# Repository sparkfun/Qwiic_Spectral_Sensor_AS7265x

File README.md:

SparkFun Triad Spectroscopy Sensor - AS7265x (Qwiic)
===========================================================

[*SparkFun Triad Spectroscopy Sensor (SEN-15050)*](https://www.sparkfun.com/products/15050)

The SparkFun Triad Spectroscopy Sensor is a powerful optical inspection sensor. Three AS7265x sensors are combined alongside a visible, UV, and IR LEDs to illuminate and test various surfaces for light spectroscopy. The Triad detects 18 discrete channels of light from 372nm (UV) to 966nm (IR) enabling desktop spectroscopy.

What can you do with light spectroscopy? It’s an amazing field of study, and the SparkFun Triad brings what used to be prohibitively expensive equipment to the desktop. The AS7265x should not be confused with highly complex mass spectrometers, but the sensor array does give the user the ability to measure and characterize how different materials absorb and reflect 18 different frequencies of light.

Want to use this board using python? Checkout hwreverse [pySectralTriad](https://github.com/hwreverse/pySpectralTriad)!

**Thanks to:**

* **pySpectralTriad** for the python application

Repository Contents
-------------------

* **/Documents** - Sensor and LED datasheets
* **/Hardware** - Eagle files

Documentation
--------------

* **[Installing an Arduino Library Guide](https://learn.sparkfun.com/tutorials/installing-an-arduino-library)** - Basic information on how to install an Arduino library.
* **[Arduino Library](https://github.com/sparkfun/SparkFun_AS7265x_Arduino_Library)** - Arduino Library for the SparkFun Triad Spectroscopy Sensor.
* **[Hookup Guide](https://learn.sparkfun.com/tutorials/spectral-triad-as7265x-hookup-guide)** - Basic hookup guide for the SparkFun Triad Spectroscopy Sensor.

License Information
-------------------

This product is _**open source**_! 

Various bits of the code have different licenses applied. Anything SparkFun wrote is beerware; if you see me (or any other SparkFun employee) at the local, and you've found our code helpful, please buy us a round!

Please use, reuse, and modify these files as you see fit. Please maintain attribution to SparkFun Electronics and release anything derivative under the same license.

Distributed as-is; no warranty is given.

- Your friends at SparkFun.

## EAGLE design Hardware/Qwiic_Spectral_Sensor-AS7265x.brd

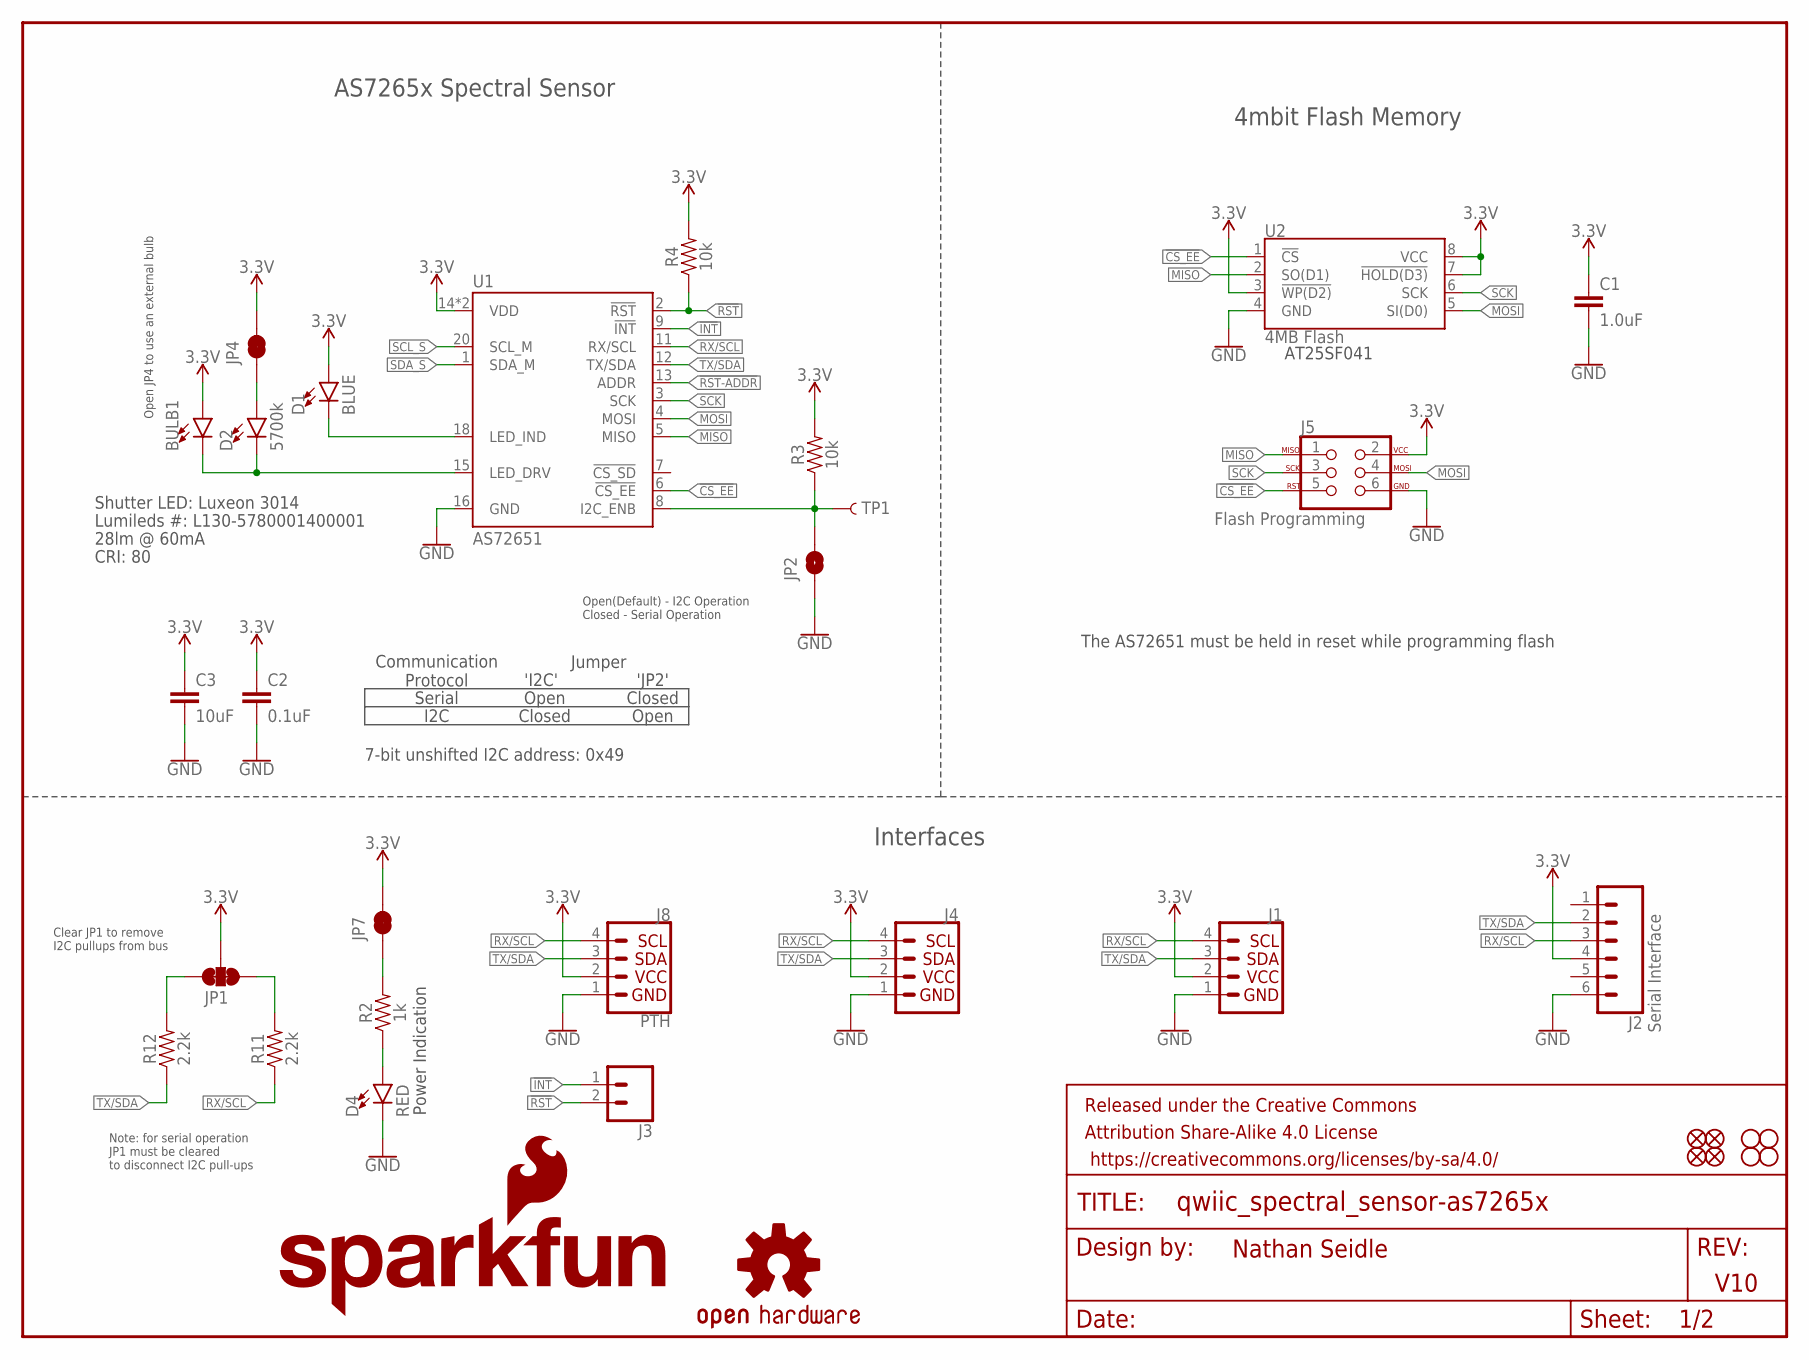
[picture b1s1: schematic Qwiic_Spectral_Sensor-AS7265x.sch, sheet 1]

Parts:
BULB1: LEDNS; LED_5MM_NOSILK
C1: 1.0uF; 0603
C2: 0.1uF; 0603
C3: 10uF; 0603
D1: BLUE; LED-0603
D2: 5700k; SUPER_BRIGHT_SMD_LED_3014
D4: RED; LED-0603
FD1, FD2, FD3, FD4: FIDUCIAL1X2; FIDUCIAL-1X2
FRAME1: FRAME-LETTER; CREATIVE_COMMONS
H1, H2, H3, H4: STAND-OFF
J1, J4: QWIIC_CONNECTORJS-1MM; 1X04_1MM_RA
J2: Serial Interface; 1X06_NO_SILK
J3: CONN_021X02_NO_SILK; 1X02_NO_SILK
J5: Flash Programming; 2X3_TEST_POINTS
J8: PTH; 1X04_NO_SILK
JP1: JUMPER-SMT_3_2-NC_TRACE_SILK; SMT-JUMPER_3_2-NC_TRACE_SILK
JP2: JUMPER-SMT_2_NO_SILK; SMT-JUMPER_2_NO_SILK
JP4, JP7: JUMPER-SMT_2_NC_TRACE_NO-SILK; SMT-JUMPER_2_NC_TRACE_NO-SILK
LOGO1: SFE_LOGO_NAME_FLAME.1_INCH; SFE_LOGO_NAME_FLAME_.1
LOGO4: OSHW-LOGOS; OSHW-LOGO-S
R2: 1k; 0603
R3, R4: 10k; 0603
R11, R12: 2.2k; 0603
TP1: TEST-POINT3; PAD.03X.03
U1: AS72651; LGA20
U2: 4MB Flash; SO08

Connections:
3.3V: BULB1.A, C1.1, C2.1, C3.1, D1.A, J1.2, J2.4, J4.2, J5.2, J8.2, JP1.2, JP4.2, JP7.2, R3.2, R4.2, U1.14 (VDD), U1.17 (VDD), U2.3 (!WP(D2)), U2.7 (!HOLD(D3)), U2.8 (VCC); also elsewhere on the board
!CS_EE: J5.5, U1.6 (!CS_EE), U2.1 (!CS)
!INT: J3.1, U1.9 (!INT)
!RST: J3.2, R4.1, U1.2 (!RST); also elsewhere on the board
!RST-ADDR: U1.13 (ADDR); also elsewhere on the board
GND: C1.2, C2.2, C3.2, D4.C, J1.1, J2.6, J4.1, J5.6, J8.1, JP2.1, U1.16 (GND), U2.4 (GND); also elsewhere on the board
I2C_ENB: JP2.2, R3.1, TP1.P$1, U1.8 (I2C_ENB)
LED_DRV: BULB1.K (C), D2.C, U1.15 (LED_DRV)
MISO: J5.1, U1.5 (MISO), U2.2 (SO(D1))
MOSI: J5.4, U1.4 (MOSI), U2.5 (SI(D0))
unnamed: JP7.1, R2.2
unnamed: D1.C, U1.18 (LED_IND)
unnamed: JP1.3, R12.2
unnamed: JP1.1, R11.2
unnamed: D2.A, JP4.1
unnamed: D4.A, R2.1
RX/SCL: J1.4, J2.3, J4.4, J8.4, R11.1, U1.11 (RX/SCL)
SCK: J5.3, U1.3 (SCK), U2.6 (SCK)
SCL_S: U1.20 (SCL_M); also elsewhere on the board
SDA_S: U1.1 (SDA_M); also elsewhere on the board
TX/SDA: J1.3, J2.2, J4.3, J8.3, R12.1, U1.12 (TX/SDA)

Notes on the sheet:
AS7265x Spectral Sensor
Open(Default) - I2C Operation Closed - Serial Operation
Clear JP1 to remove I2C pullups from bus
V10
Nathan Seidle
4mbit Flash Memory
Interfaces
Note: for serial operation JP1 must be cleared to disconnect I2C pull-ups
The AS72651 must be held in reset while programming flash
Open JP4 to use an external bulb
Serial
'I2C'
'JP2'
Open
Closed
Communication Protocol
I2C
Lumileds #: L130-5780001400001
Shutter LED: Luxeon 3014
28lm @ 60mA
CRI: 80
7-bit unshifted I2C address: 0x49
Power Indication
AT25SF041
Jumper

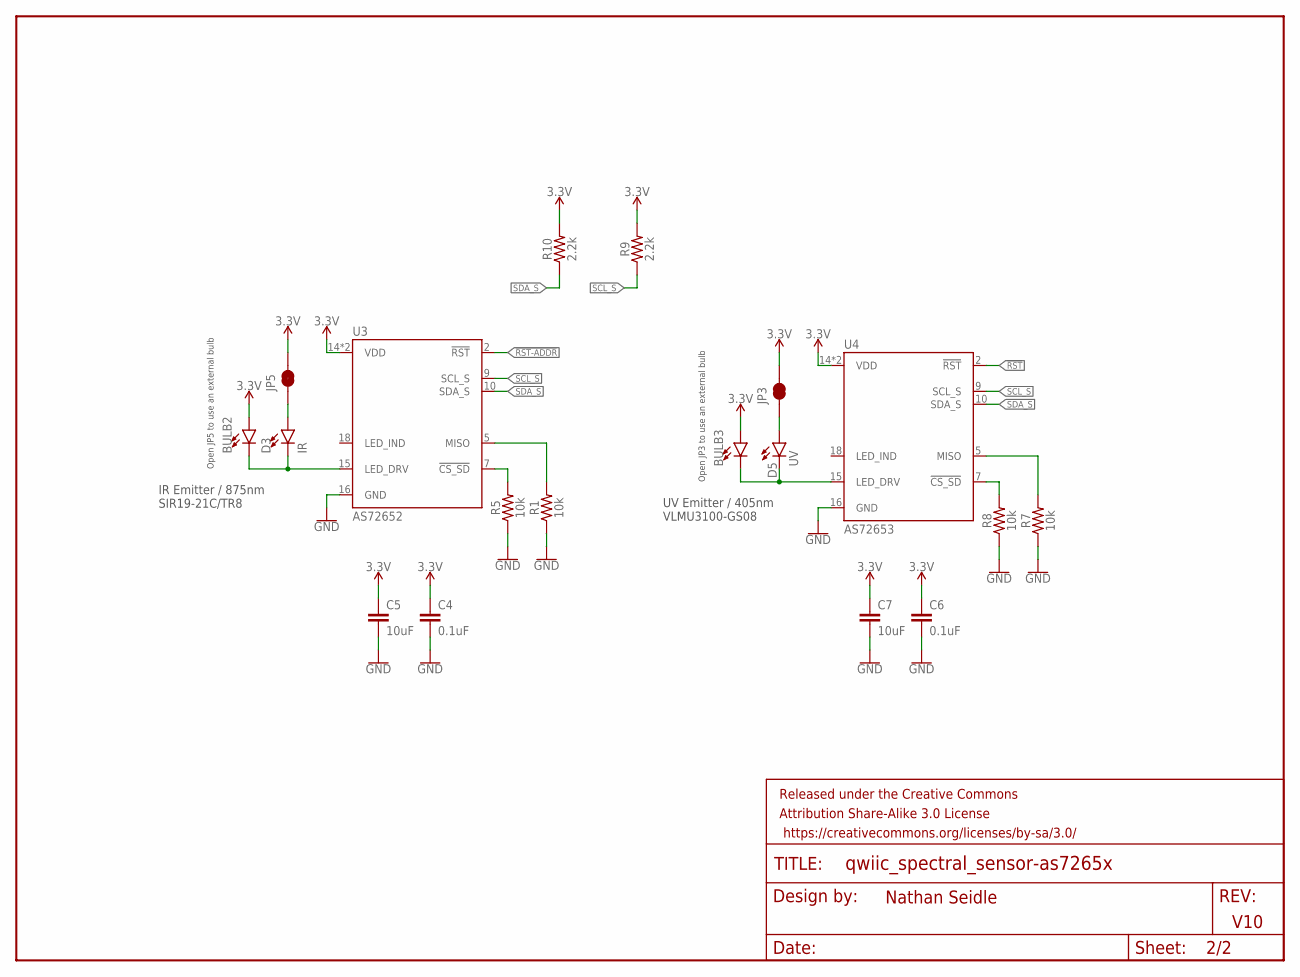
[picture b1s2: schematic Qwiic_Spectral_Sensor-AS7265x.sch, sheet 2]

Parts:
BULB2, BULB3: LEDNS; LED_5MM_NOSILK
C4, C6: 0.1uF; 0603
C5, C7: 10uF; 0603
D3: IR; LED-0603
D5: UV; PLCC-2
FRAME3: FRAME-LETTER; CREATIVE_COMMONS
JP3, JP5: JUMPER-SMT_2_NC_TRACE_NO-SILK; SMT-JUMPER_2_NC_TRACE_NO-SILK
R1, R5, R7, R8: 10k; 0603
R9, R10: 2.2k; 0603
U3: AS72652; LGA20
U4: AS72653; LGA20

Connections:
3.3V: BULB2.A, BULB3.A, C4.1, C5.1, C6.1, C7.1, JP3.2, JP5.2, R9.2, R10.2, U3.14 (VDD), U3.17 (VDD), U4.14 (VDD), U4.17 (VDD); also elsewhere on the board
!RST: U4.2 (!RST); also elsewhere on the board
!RST-ADDR: U3.2 (!RST); also elsewhere on the board
GND: C4.2, C5.2, C6.2, C7.2, R1.1, R5.1, R7.1, R8.1, U3.16 (GND), U4.16 (GND); also elsewhere on the board
LED_DRV1: BULB2.K (C), D3.C, U3.15 (LED_DRV)
LED_DRV2: BULB3.K (C), D5.C, U4.15 (LED_DRV)
unnamed: R5.2, U3.7 (!CS_SD)
unnamed: D3.A, JP5.1
unnamed: R1.2, U3.5 (MISO)
unnamed: D5.A, JP3.1
unnamed: R8.2, U4.7 (!CS_SD)
unnamed: R7.2, U4.5 (MISO)
SCL_S: R9.1, U3.9 (SCL_S), U4.9 (SCL_S); also elsewhere on the board
SDA_S: R10.1, U3.10 (SDA_S), U4.10 (SDA_S); also elsewhere on the board

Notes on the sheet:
Open JP5 to use an external bulb
Open JP3 to use an external bulb
IR Emitter / 875nm SIR19-21C/TR8
UV Emitter / 405nm VLMU3100-GS08
V10
Nathan Seidle

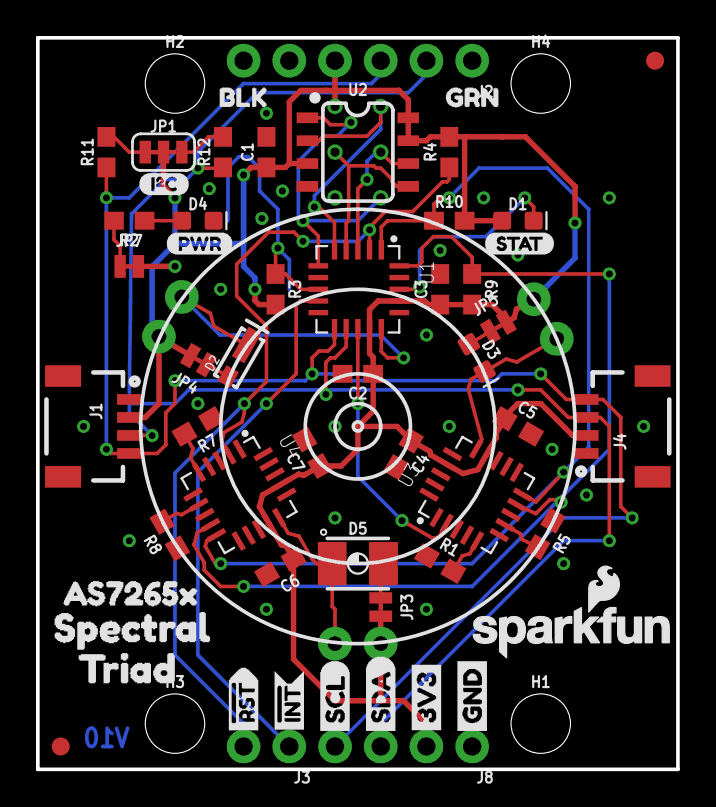
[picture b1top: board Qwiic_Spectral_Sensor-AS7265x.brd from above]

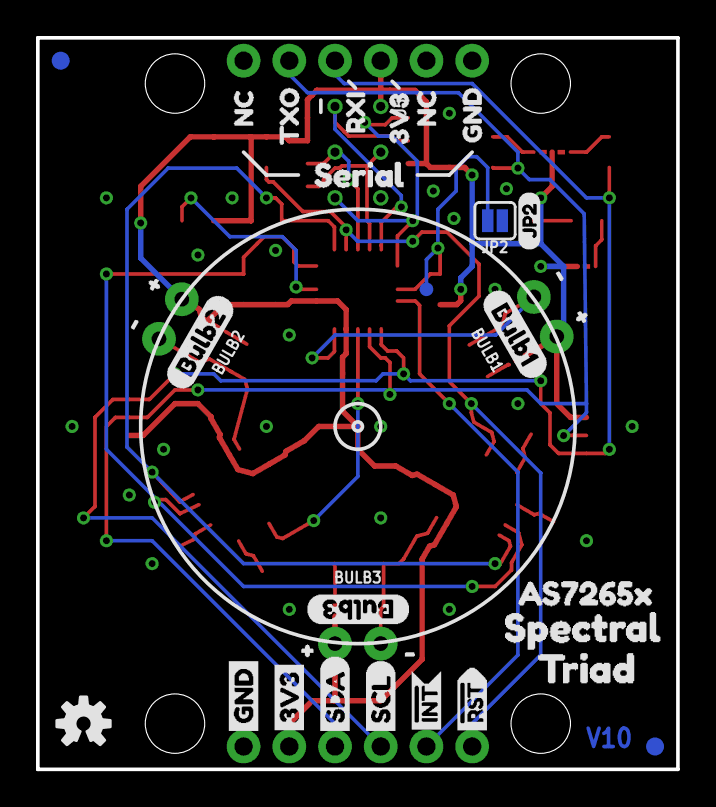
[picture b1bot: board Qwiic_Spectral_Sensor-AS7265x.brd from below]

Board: 2 copper layers, 35.6 x 40.6 mm, 95 parts (35 on the bottom side), 29 nets.

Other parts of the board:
U$1, U$36, U$37: #0
U$2: I_SUPER2_C-()-03
U$3: PWR-()-03
U$4, U$14: AS7265X0
U$5: BULB15
U$6: BULB26
U$7: BULB37
U$8: JP20
U$9, U$13: SPECTRAL1
U$10: STAT4
U$11, U$12: TRIAD2
U$15: 3V33
U$16: BLK7
U$17: GND5
U$18: GRN6
U$19, U$20: NC4
U$21: RXI2
U$22: SERIAL0
U$23: TXO1
U$24, U$31: 3V3-04
U$25, U$30: GND-04
U$26, U$32: SDA-[)
U$27, U$33: SCL-[)
U$28, U$34: INT#-[<-04
U$29, U$35: RST#-[>-04
U$38, U$39, U$40: #1

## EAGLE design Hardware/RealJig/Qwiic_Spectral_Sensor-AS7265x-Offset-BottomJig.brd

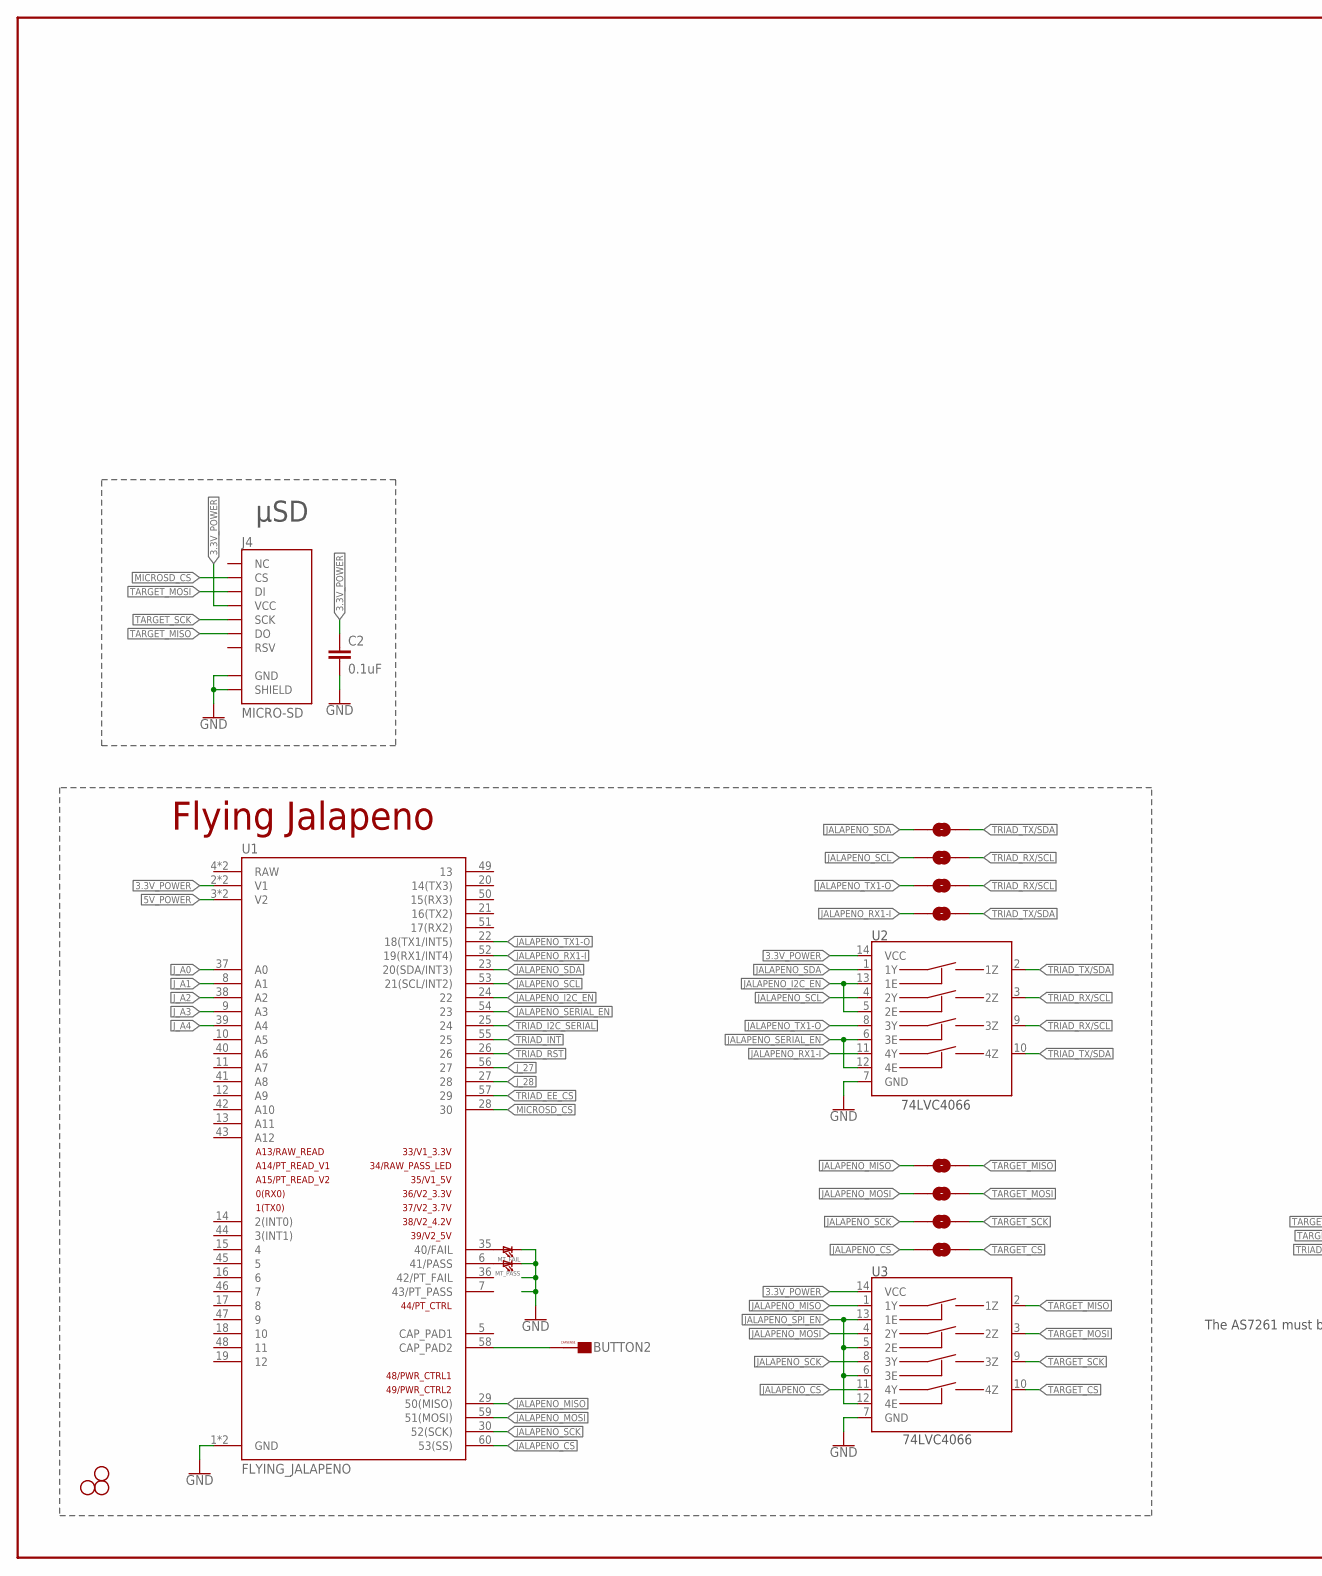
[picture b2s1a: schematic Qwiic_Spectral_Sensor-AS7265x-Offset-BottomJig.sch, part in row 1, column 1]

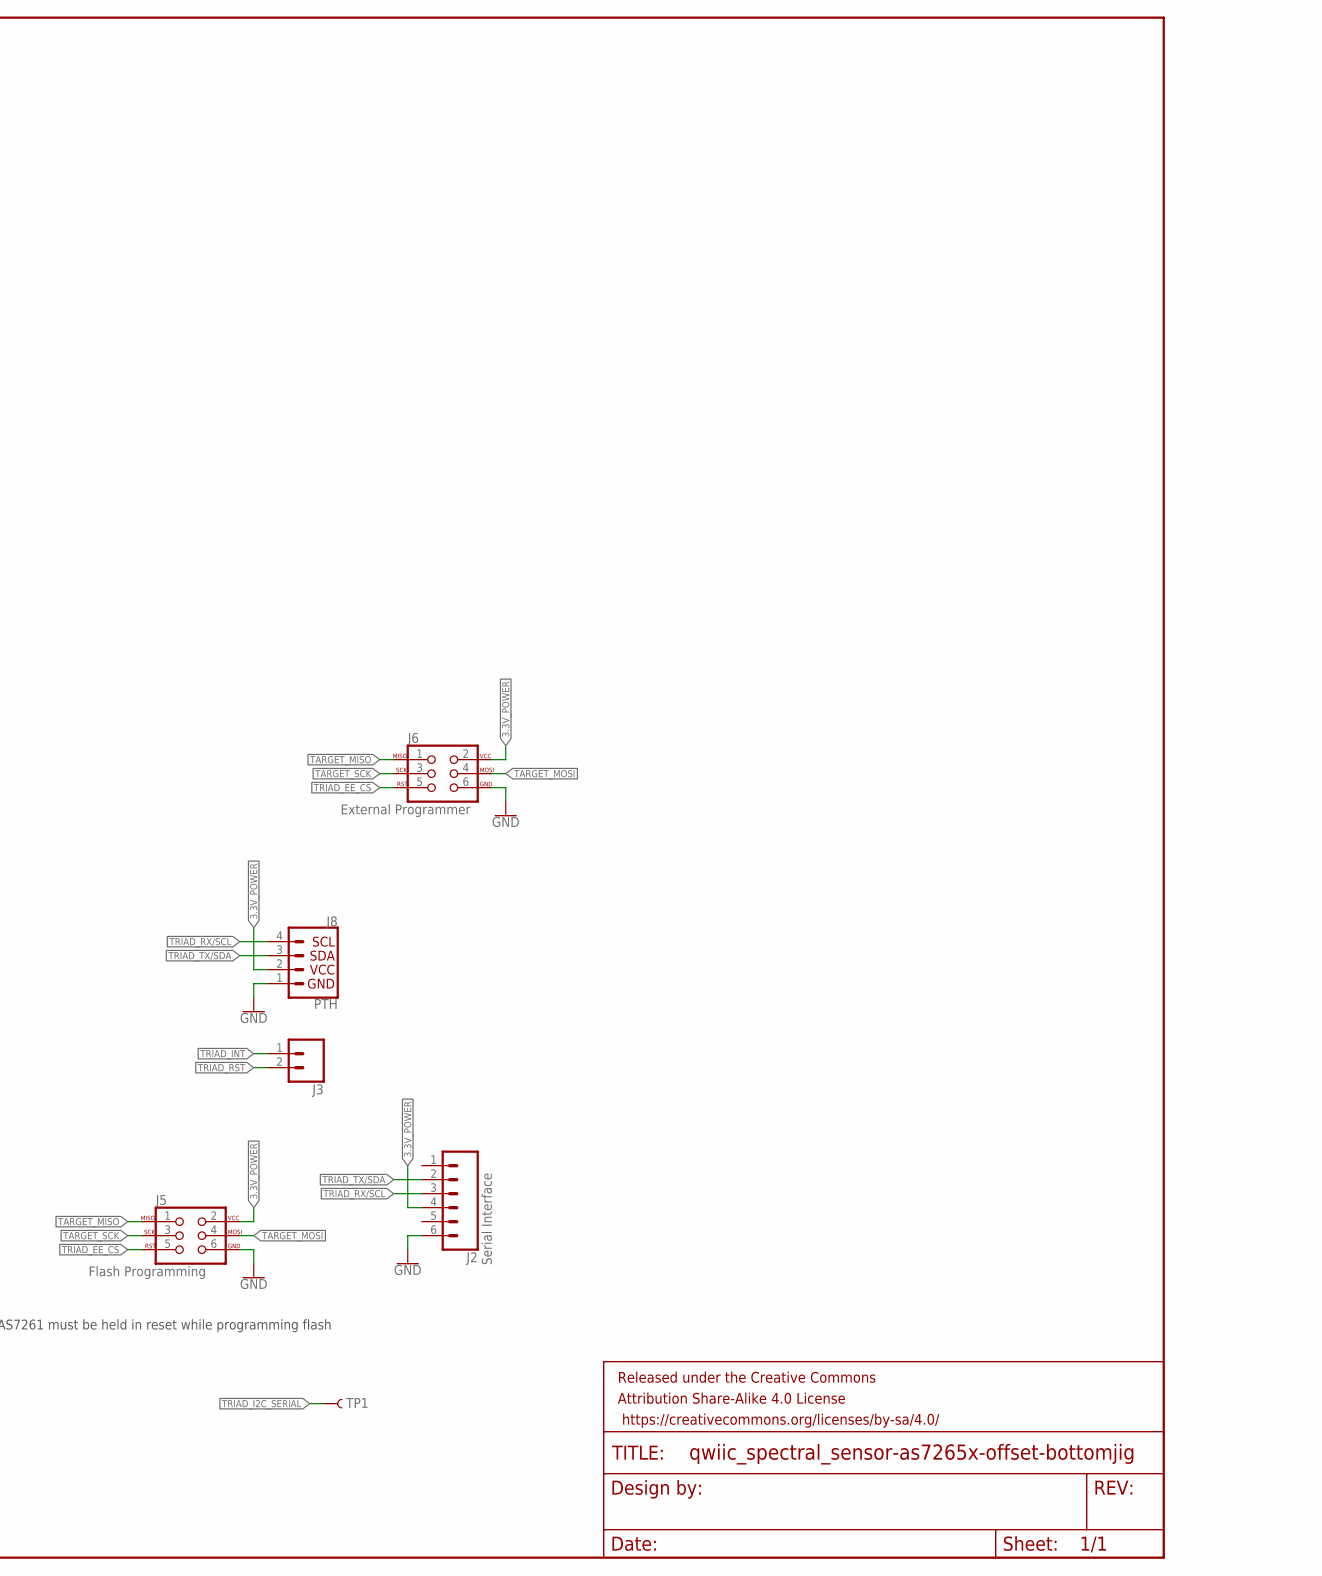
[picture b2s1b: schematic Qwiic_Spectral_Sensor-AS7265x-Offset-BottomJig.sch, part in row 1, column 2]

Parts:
BUTTON2: CAPSENSE_BUTTON_PAD_ONLY; CAPSENSE_BUTTON_PADS_ONLY
C2: 0.1uF; 0603
FRAME2: FRAME-LEDGER; CREATIVE_COMMONS
H1, H3, H4: STAND-OFF
J2: Serial Interface; 1X06_NO_SILK
J3: CONN_021X02_NO_SILK; 1X02_NO_SILK
J4: MICRO-SD; MICRO-SD-SOCKET
J5: Flash Programming; 2X3-NS
J6: External Programmer; 2X3-NS
J8: PTH; 1X04_NO_SILK
J_SCL, J_SCL1, J_SCL2, J_SCL3, J_SCL4, J_SCL5: JUMPER-SMT_2_NO_NO-SILK; SMT-JUMPER_2_NO_NO-SILK
J_SDA, J_SDA1: JUMPER-SMT_2_NO_NO-SILK; SMT-JUMPER_2_NO_NO-SILK
MT_FAIL: LED1206; LED-1206
MT_PASS: LED1206; LED-1206
TP1: TEST-POINTPOGO_PTH; 1X01_NO_SILK
U1: FLYING_JALAPENO; FLYING_JALAPENO_V3_M
U2, U3: 74LVC4066; SO14

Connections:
3.3V_POWER: C2.1, J2.4, J4.VCC, J5.2, J6.2, J8.2, U1.2 (V1), U1.32 (V1), U2.14 (VCC), U3.14 (VCC)
5V_POWER: U1.3 (V2), U1.33 (V2)
BUTTON2: BUTTON2.CAPSENSE_PAD, U1.58 (CAP_PAD2)
GND: C2.2, J2.6, J4.CD1 (SHIELD), J4.GND, J5.6, J6.6, J8.1, MT_FAIL.C, MT_PASS.C, U1.1 (GND), U1.31 (GND), U2.7 (GND), U3.7 (GND)
JALAPENO_CS: J_SDA1.1, U1.60 (53(SS)), U3.11 (4Y)
JALAPENO_I2C_EN: U1.24 (22), U2.5 (2E), U2.13 (1E)
JALAPENO_MISO: J_SCL5.1, U1.29 (50(MISO)), U3.1 (1Y)
JALAPENO_MOSI: J_SCL3.1, U1.59 (51(MOSI)), U3.4 (2Y)
JALAPENO_RX1-I: J_SDA.1, U1.52 (19(RX1/INT4)), U2.11 (4Y)
JALAPENO_SCK: J_SCL4.1, U1.30 (52(SCK)), U3.8 (3Y)
JALAPENO_SCL: J_SCL.1, U1.53 (21(SCL/INT2)), U2.4 (2Y)
JALAPENO_SDA: J_SCL2.1, U1.23 (20(SDA/INT3)), U2.1 (1Y)
JALAPENO_SERIAL_EN: U1.54 (23), U2.6 (3E), U2.12 (4E)
JALAPENO_SPI_EN: U3.5 (2E), U3.6 (3E), U3.12 (4E), U3.13 (1E)
JALAPENO_TX1-O: J_SCL1.1, U1.22 (18(TX1/INT5)), U2.8 (3Y)
J_27: U1.56 (27)
J_28: U1.27 (28)
J_A0: U1.37 (A0)
J_A1: U1.8 (A1)
J_A2: U1.38 (A2)
J_A3: U1.9 (A3)
J_A4: U1.39 (A4)
MICROSD_!CS!: J4.CS, U1.28 (30)
unnamed: MT_PASS.A, U1.6 (41/PASS)
unnamed: MT_FAIL.A, U1.35 (40/FAIL)
TARGET_CS: J_SDA1.2, U3.10 (4Z)
TARGET_MISO: J4.DO, J5.1, J6.1, J_SCL5.2, U3.2 (1Z)
TARGET_MOSI: J4.DI, J5.4, J6.4, J_SCL3.2, U3.3 (2Z)
TARGET_SCK: J4.SCLK (SCK), J5.3, J6.3, J_SCL4.2, U3.9 (3Z)
TRIAD_!INT!: J3.1, U1.55 (25)
TRIAD_!RST!: J3.2, U1.26
TRIAD_EE_!CS!: J5.5, J6.5, U1.57 (29)
TRIAD_I2C_!SERIAL!: TP1.1, U1.25 (24)
TRIAD_RX/SCL: J2.3, J8.4, J_SCL.2, J_SCL1.2, U2.3 (2Z), U2.9 (3Z)
TRIAD_TX/SDA: J2.2, J8.3, J_SCL2.2, J_SDA.2, U2.2 (1Z), U2.10 (4Z)

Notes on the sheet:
The AS7261 must be held in reset while programming flash
Flying Jalapeno
μSD

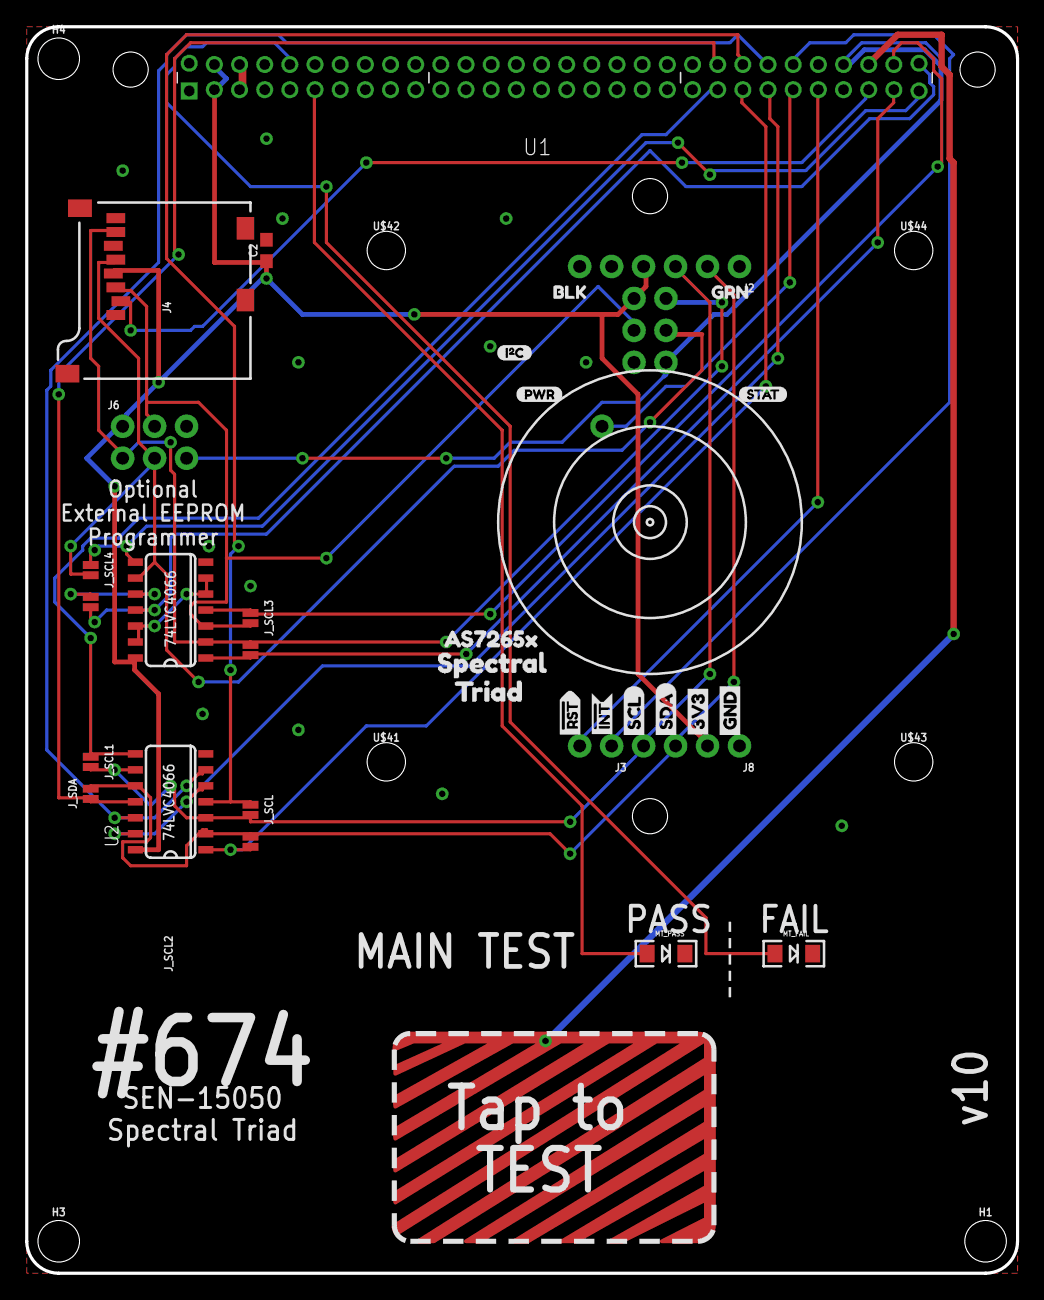
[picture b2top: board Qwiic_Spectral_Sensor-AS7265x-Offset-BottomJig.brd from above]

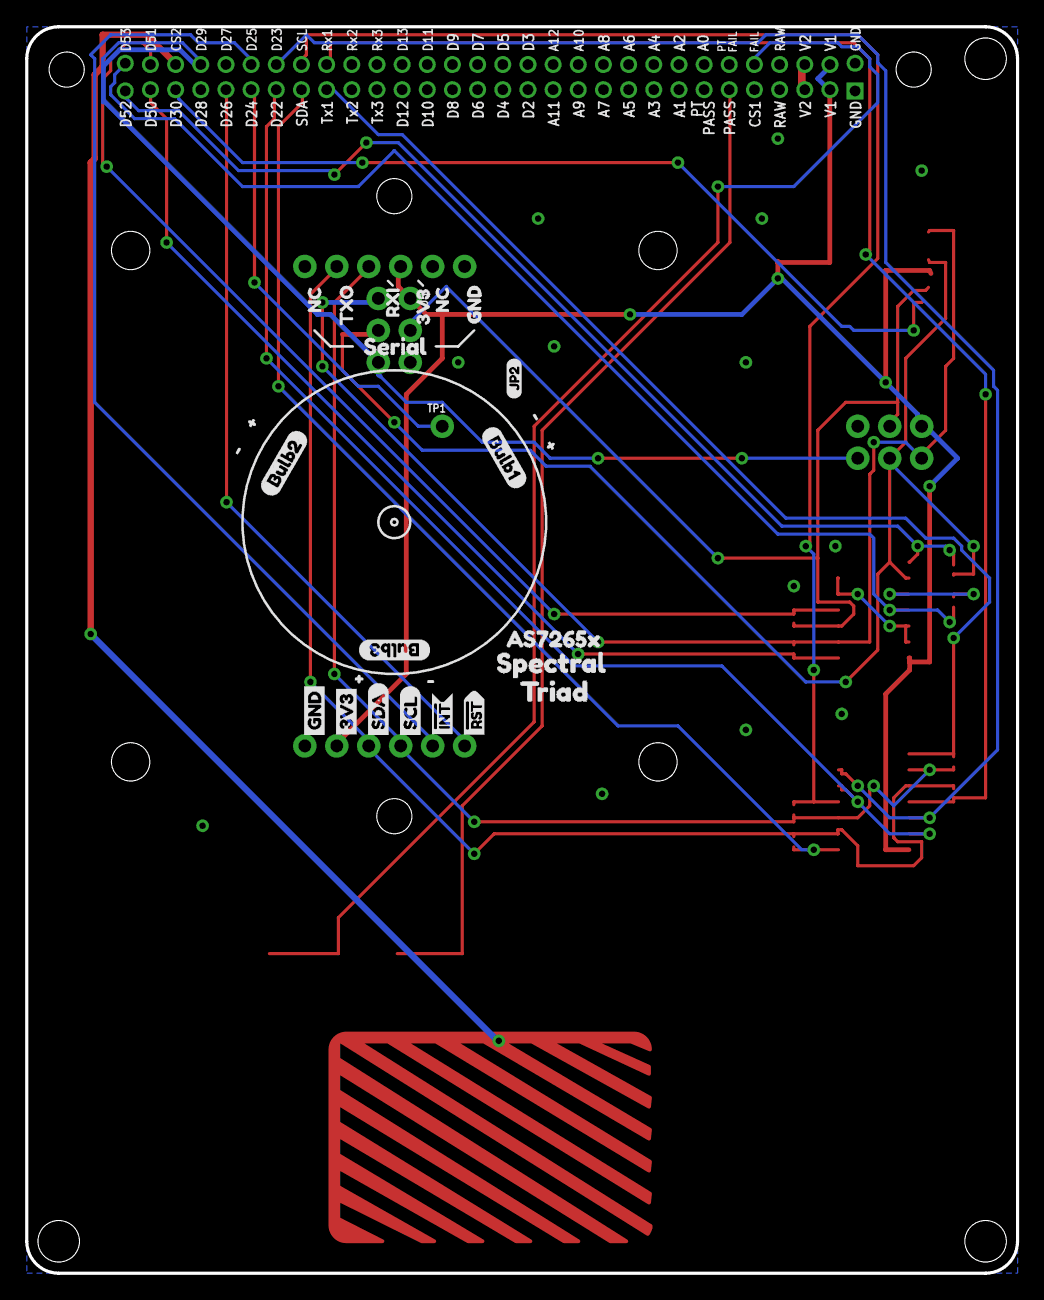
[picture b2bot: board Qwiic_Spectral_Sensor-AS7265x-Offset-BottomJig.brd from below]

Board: 2 copper layers, 78.7 x 99.1 mm, 72 parts (28 on the bottom side), 28 nets.

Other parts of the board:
U$1, U$36, U$37: #0
U$2: I_SUPER2_C-()-03
U$3: PWR-()-03
U$4, U$14: AS7265X0
U$5: BULB15
U$6: BULB26
U$7: BULB37
U$8: JP20
U$9, U$13: SPECTRAL1
U$10: STAT4
U$11, U$12: TRIAD2
U$15: 3V33
U$16: BLK7
U$17: GND5
U$18: GRN6
U$19, U$20: NC4
U$21: RXI2
U$22: SERIAL0
U$23: TXO1
U$24, U$31: 3V3-04
U$25, U$30: GND-04
U$26, U$32: SDA-[)
U$27, U$33: SCL-[)
U$28, U$34: INT#-[<-04
U$29, U$35: RST#-[>-04
U$38, U$39, U$40: #1
U$41, U$42, U$43, U$44: STAND-OFF-TIGHT
U$45, U$46: NUBBIN_LOCKER

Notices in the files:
parts and their libraries:
SparkFun-Aesthetics: Licensing: Creative Commons ShareAlike 4.0 International - https://creativecommons.org/licenses/by-sa/4.0
SparkFun-Aesthetics: Released under the Creative Commons Attribution Share-Alike 4.0 License
SparkFun-Aesthetics: https://creativecommons.org/licenses/by-sa/4.0
